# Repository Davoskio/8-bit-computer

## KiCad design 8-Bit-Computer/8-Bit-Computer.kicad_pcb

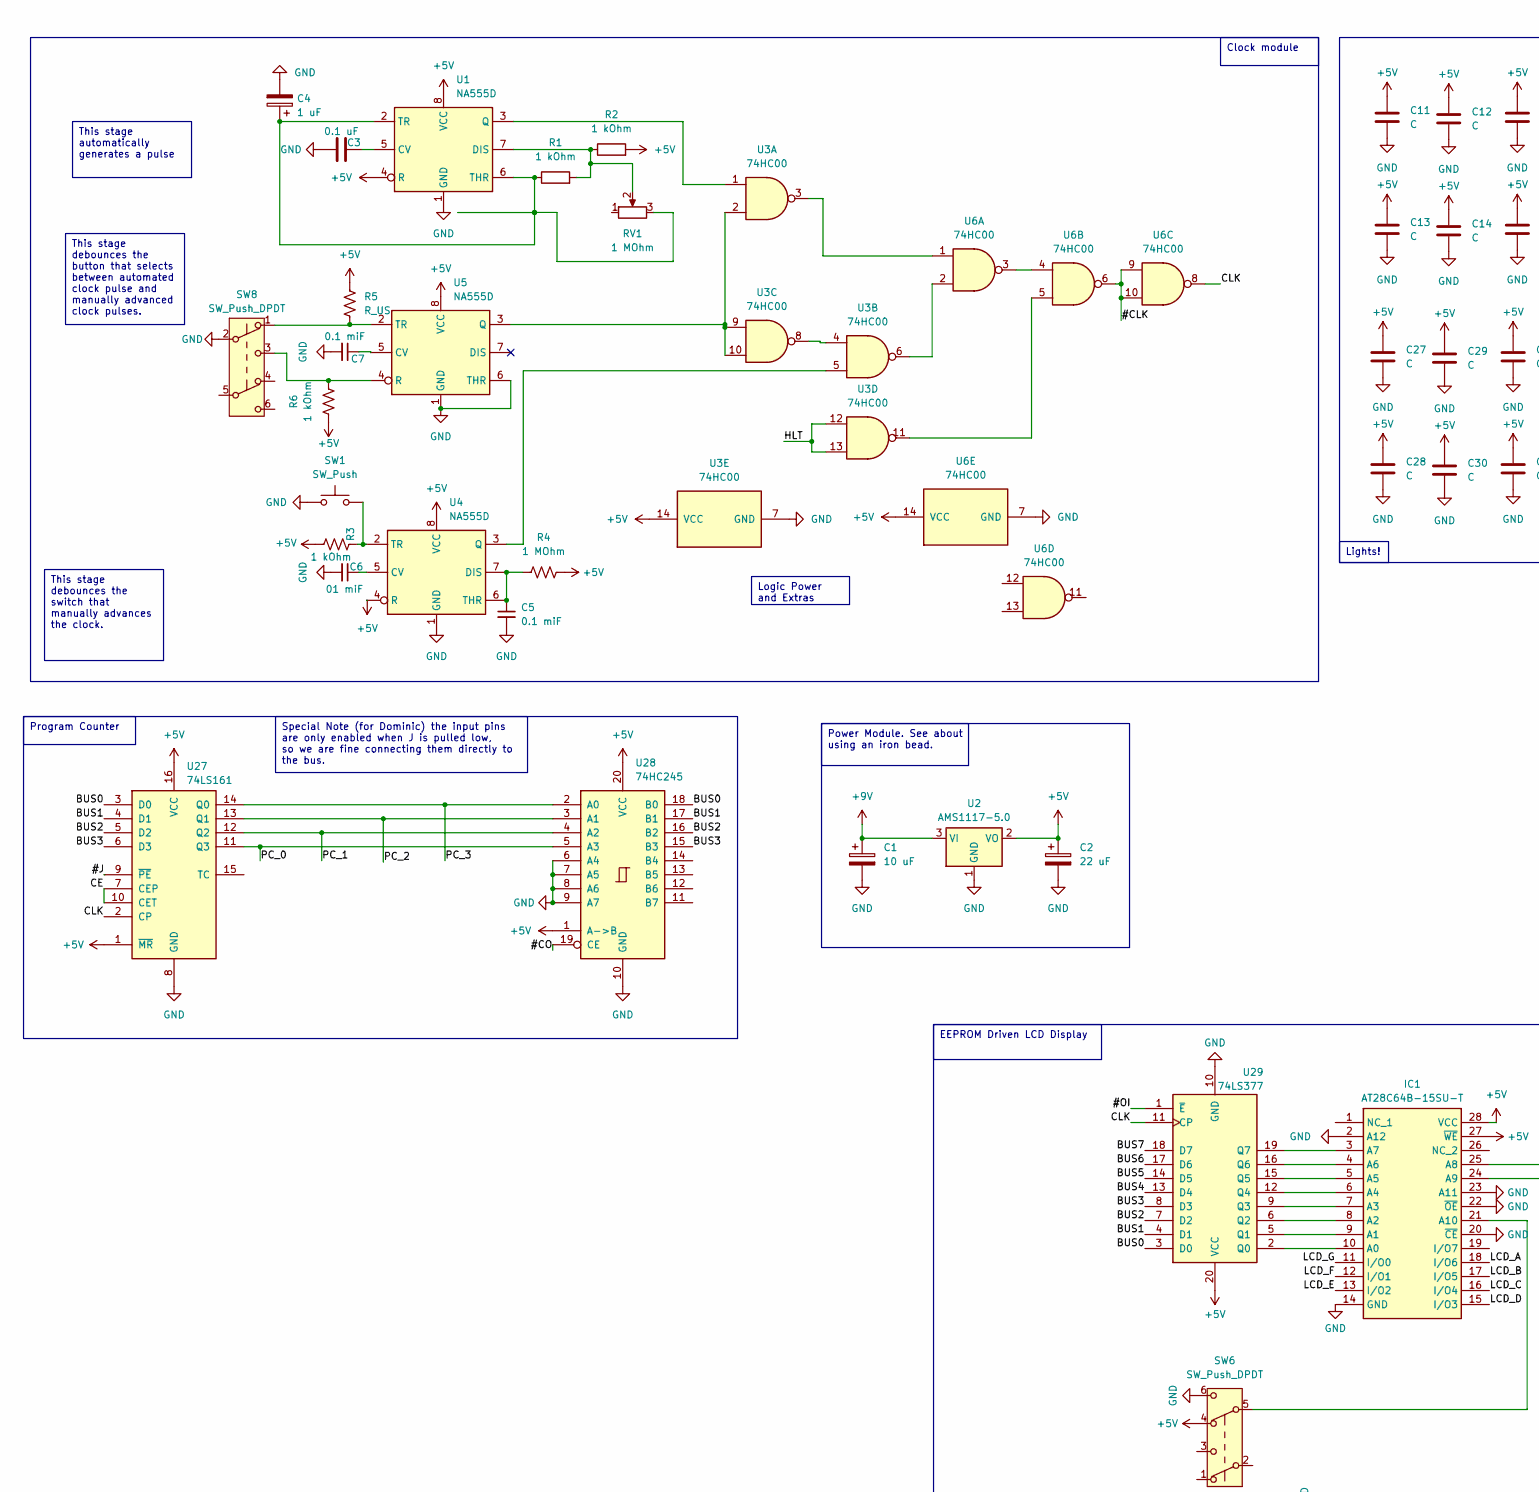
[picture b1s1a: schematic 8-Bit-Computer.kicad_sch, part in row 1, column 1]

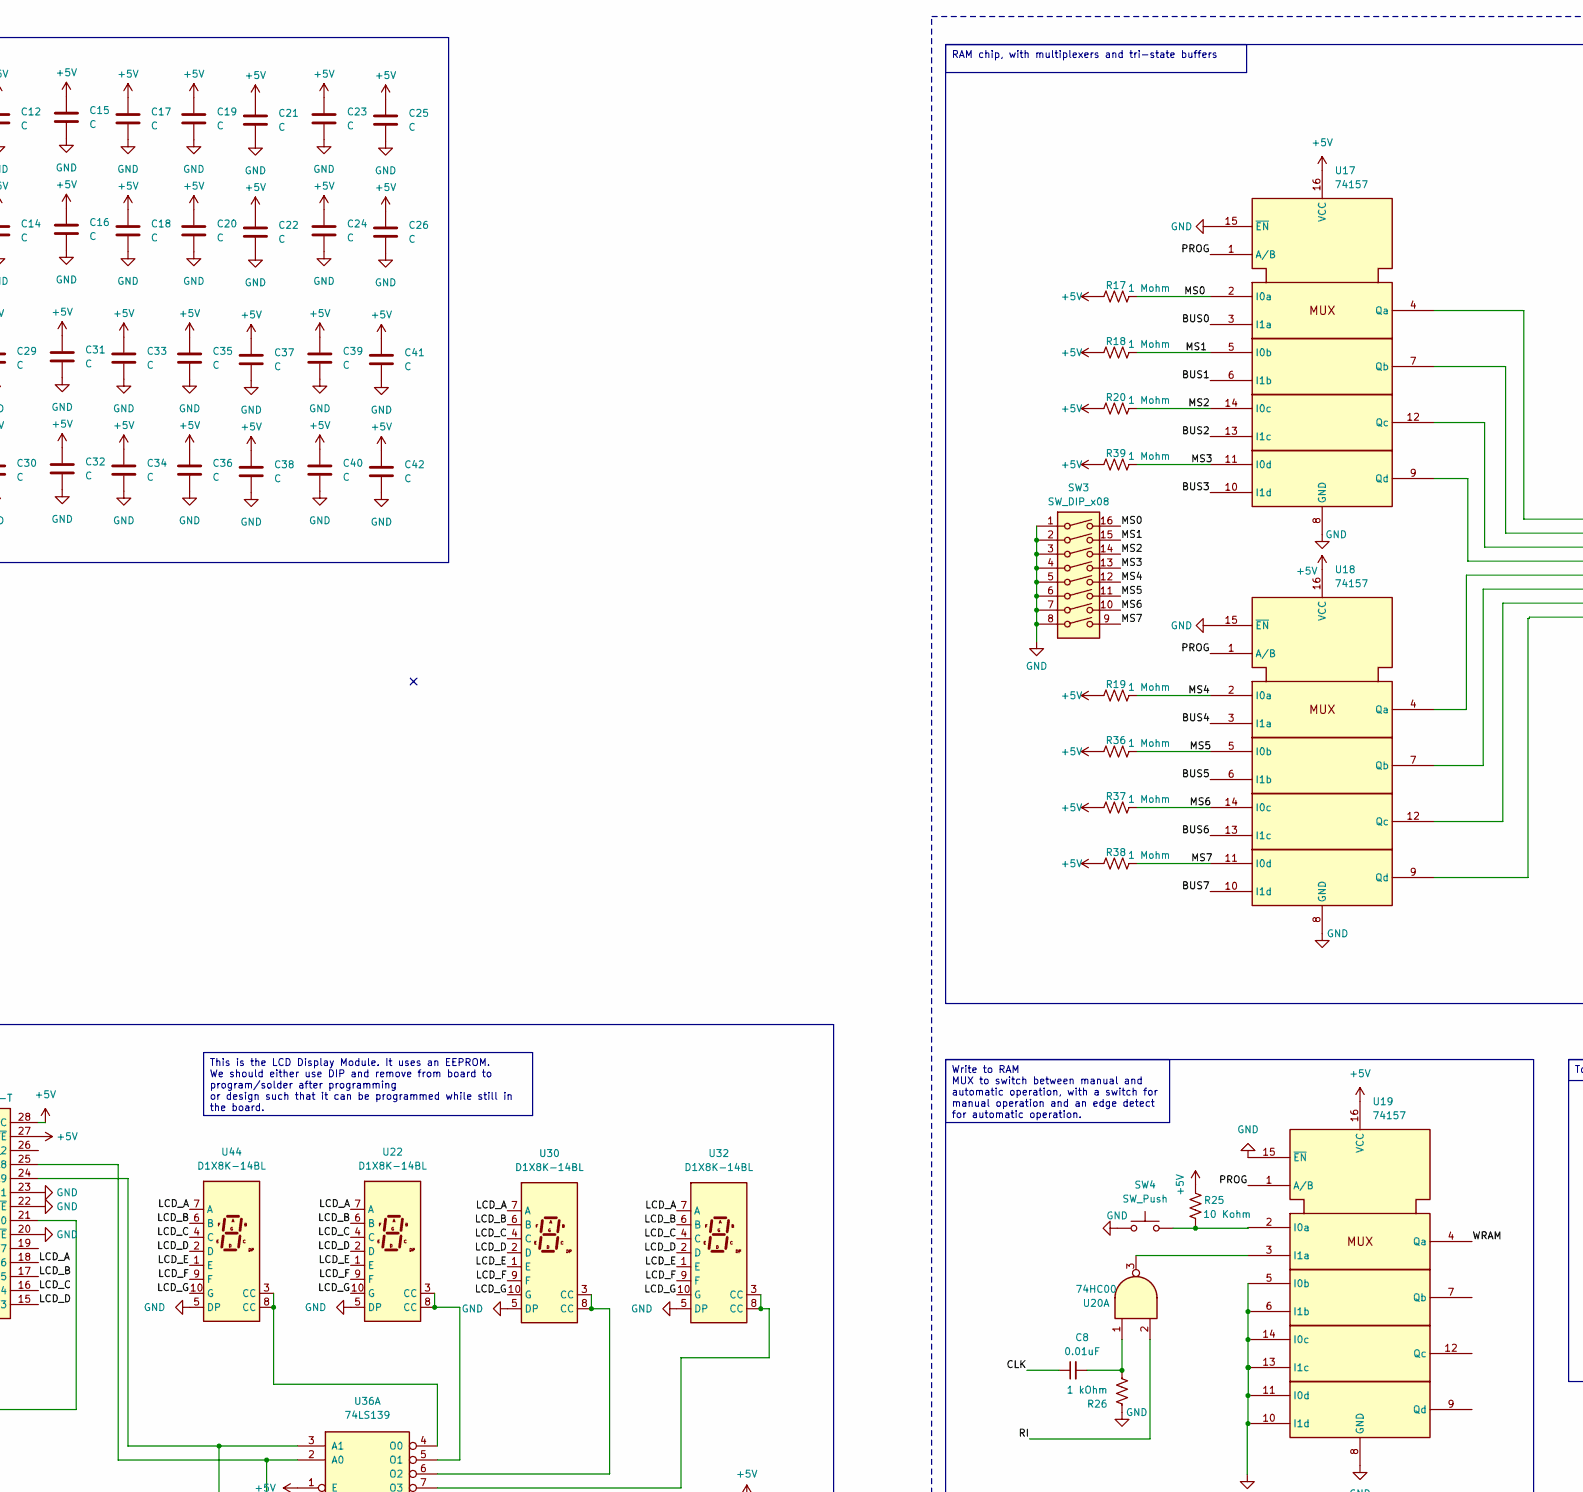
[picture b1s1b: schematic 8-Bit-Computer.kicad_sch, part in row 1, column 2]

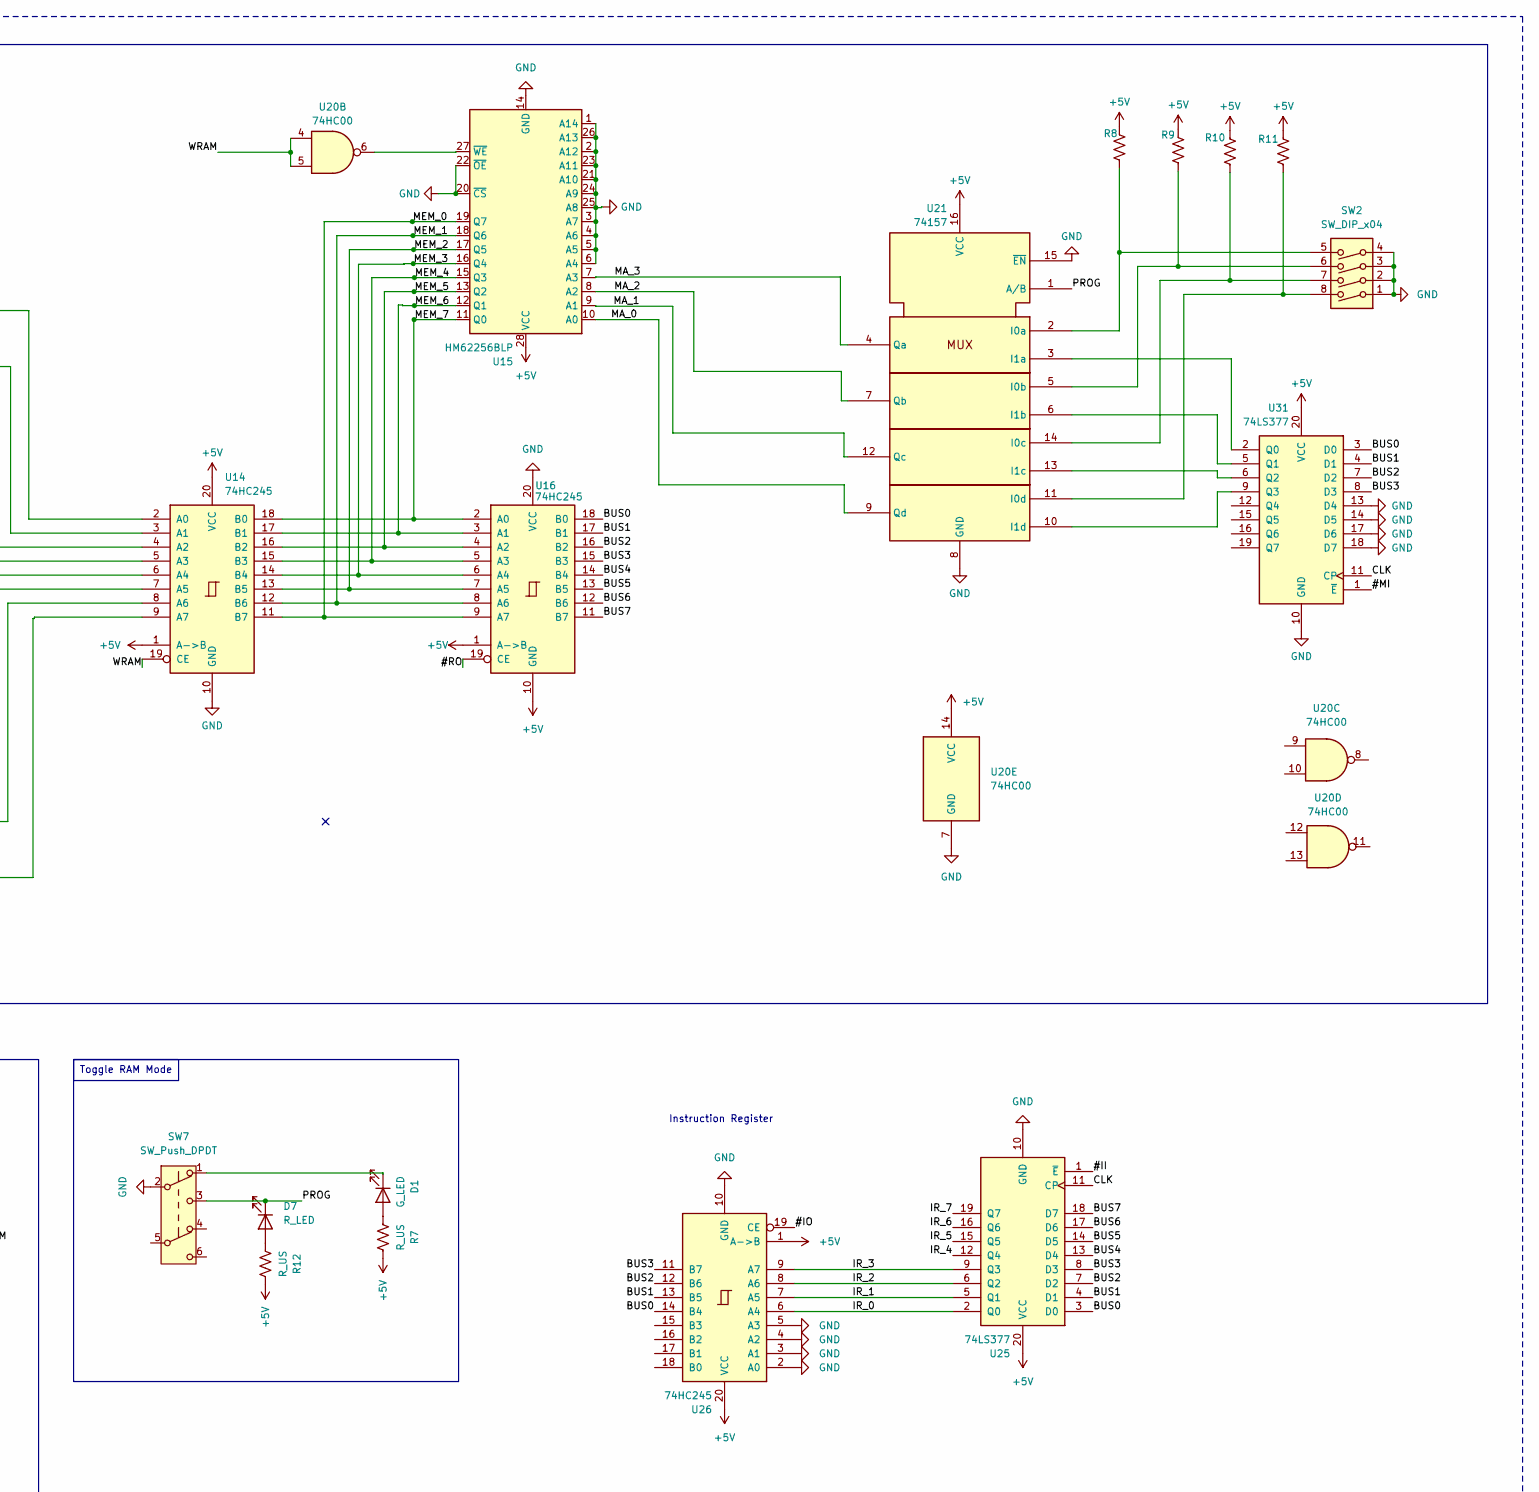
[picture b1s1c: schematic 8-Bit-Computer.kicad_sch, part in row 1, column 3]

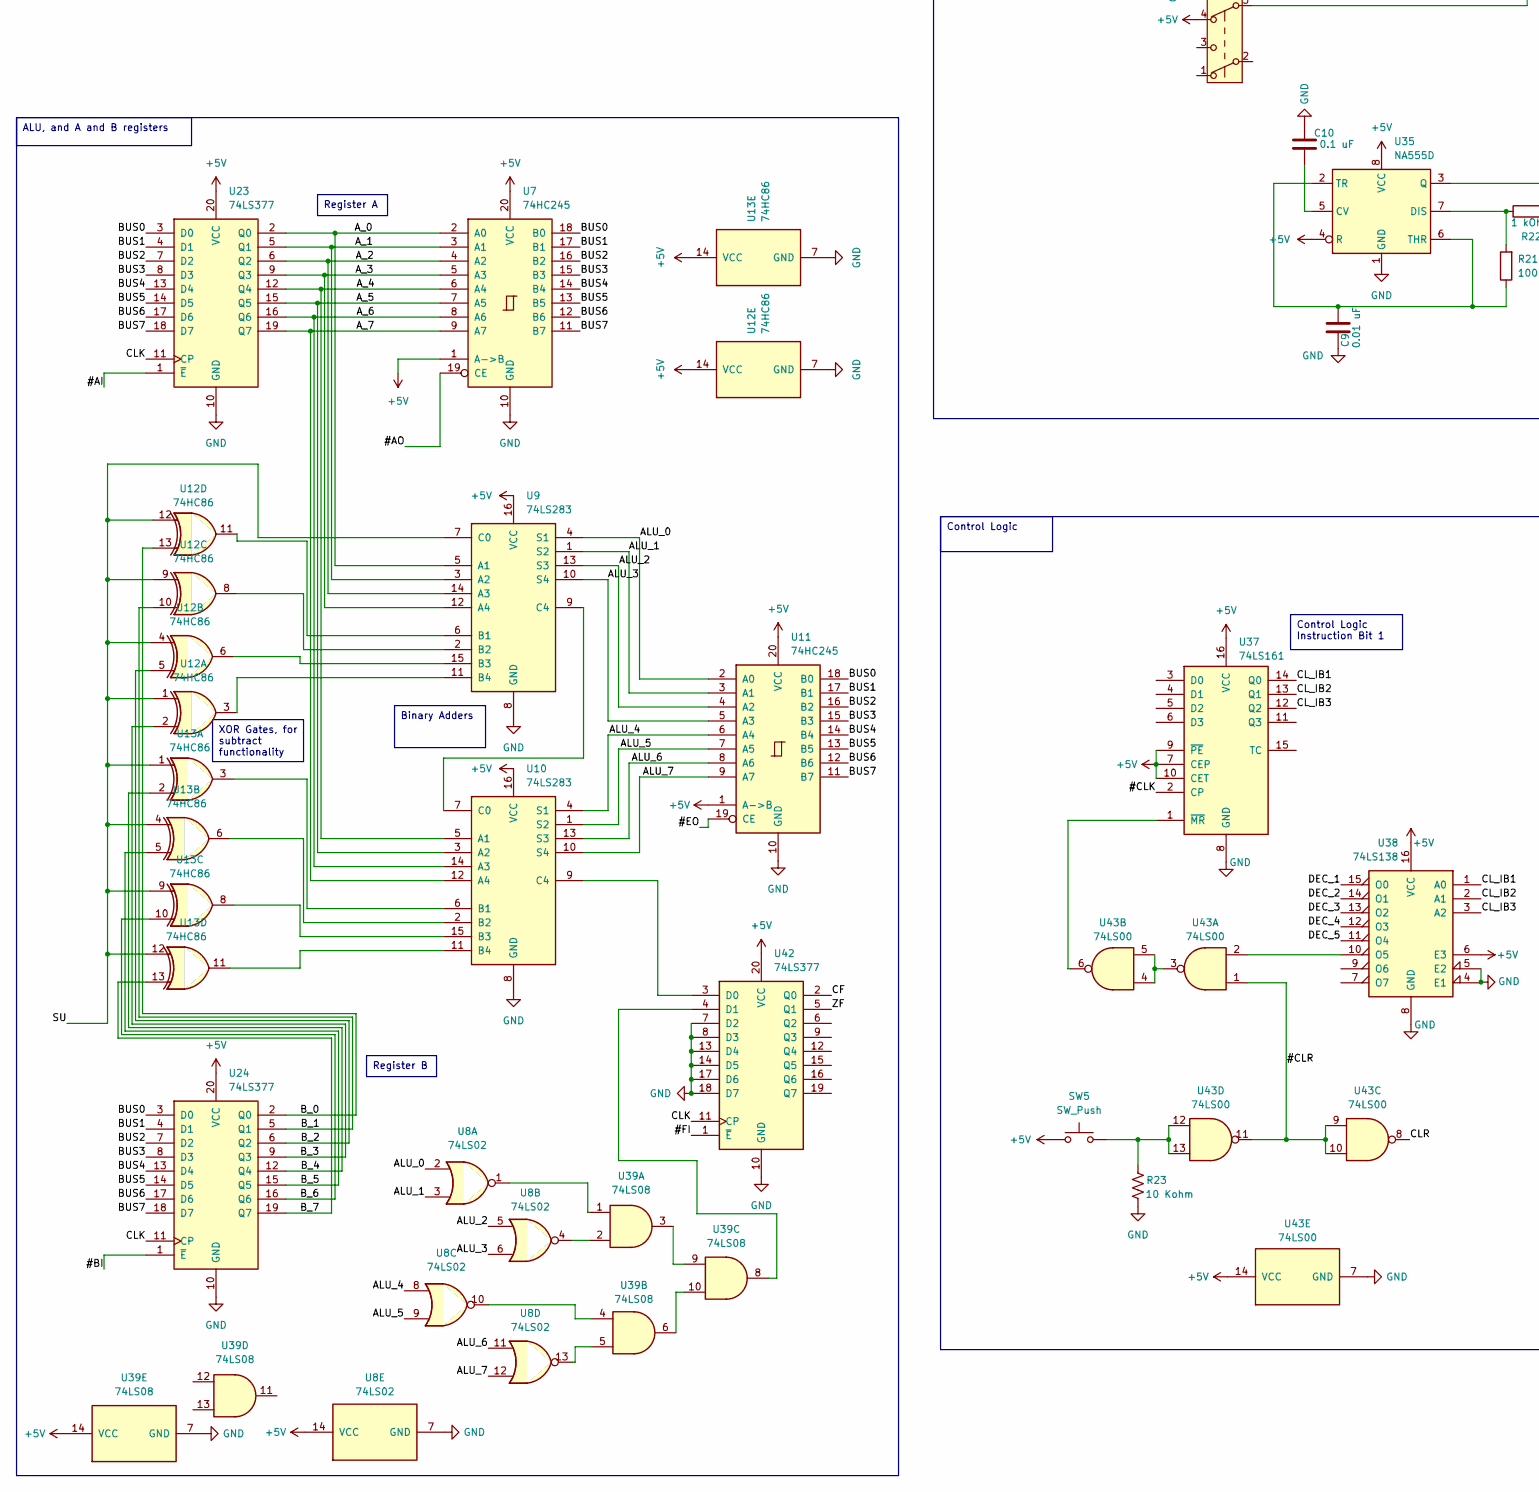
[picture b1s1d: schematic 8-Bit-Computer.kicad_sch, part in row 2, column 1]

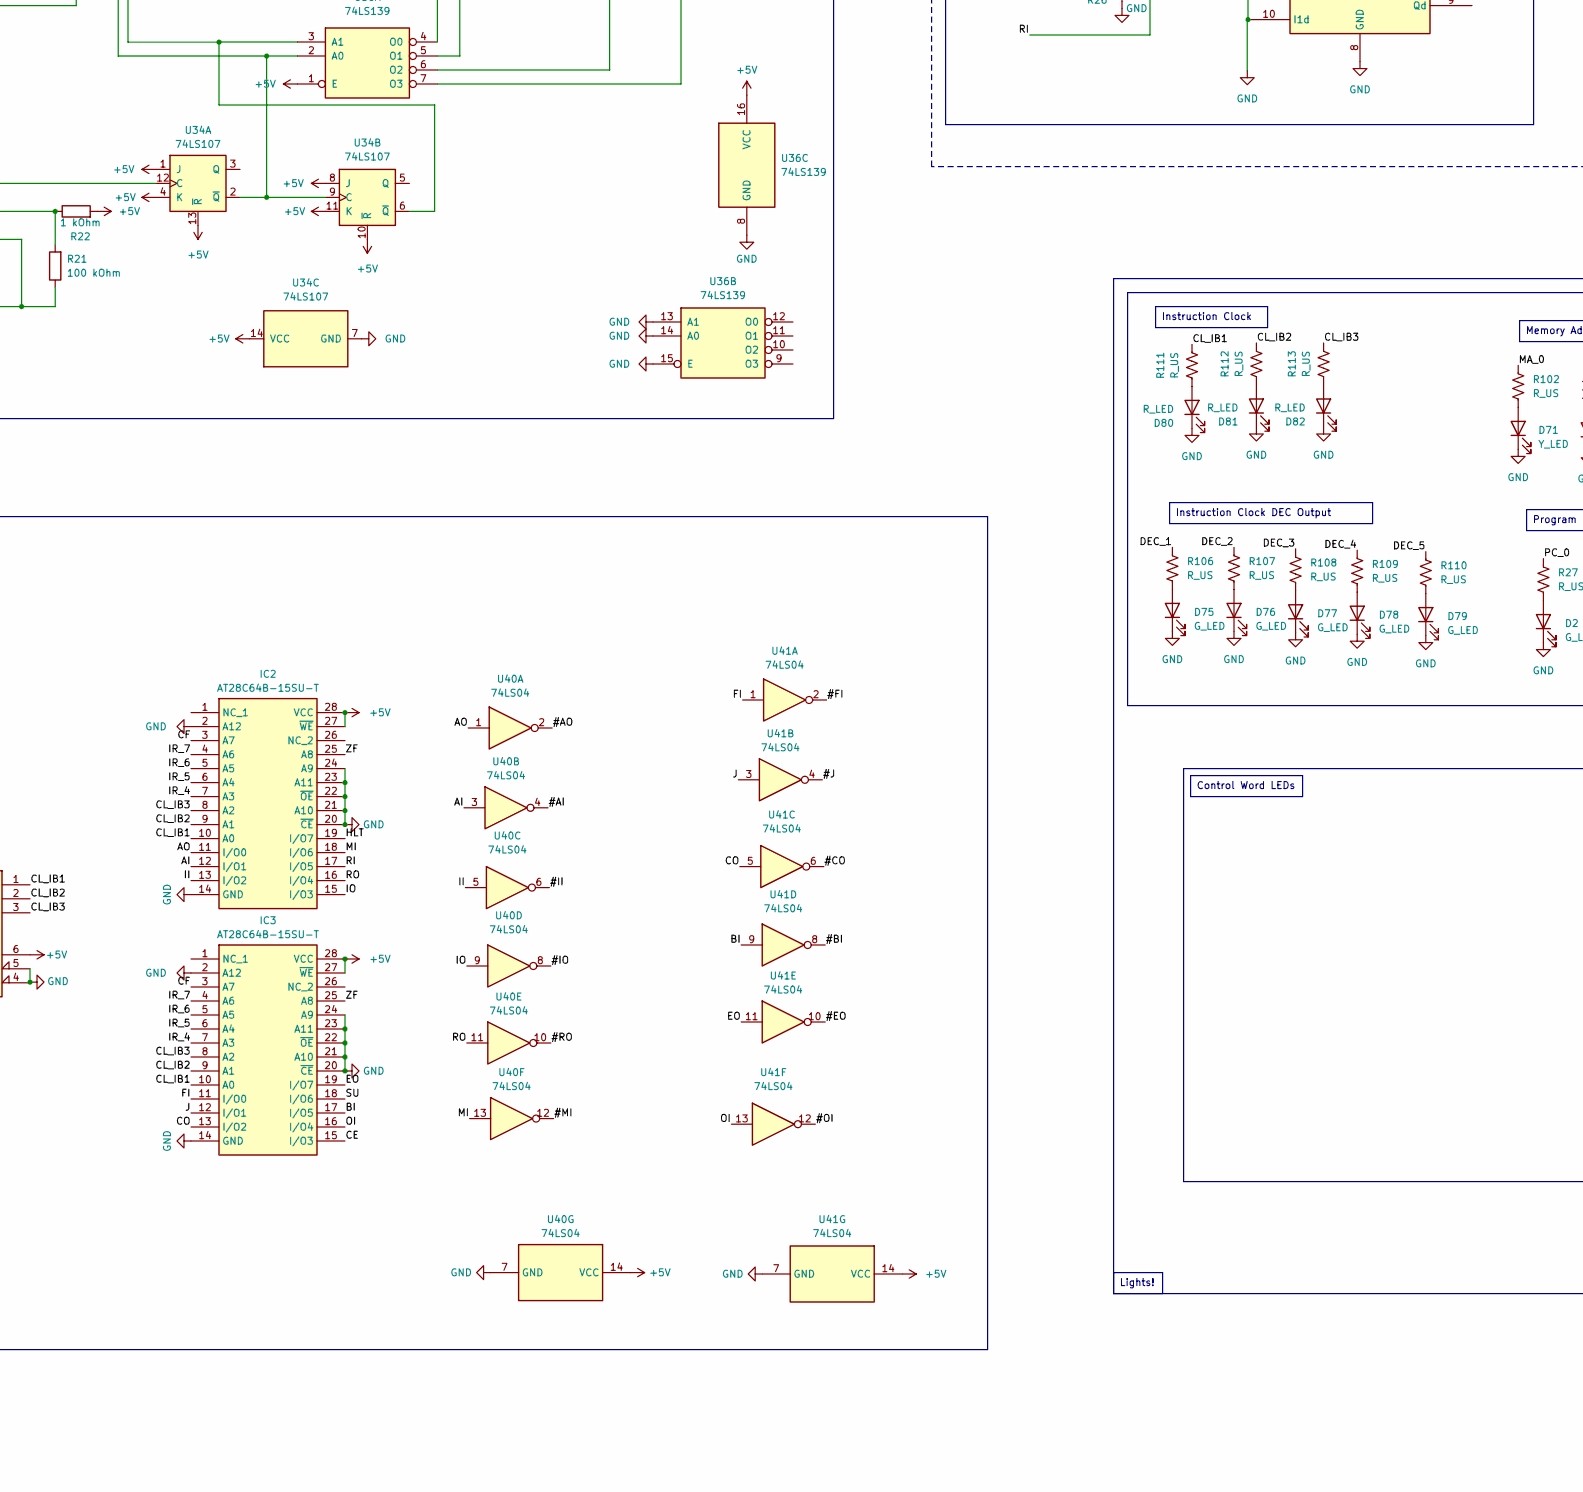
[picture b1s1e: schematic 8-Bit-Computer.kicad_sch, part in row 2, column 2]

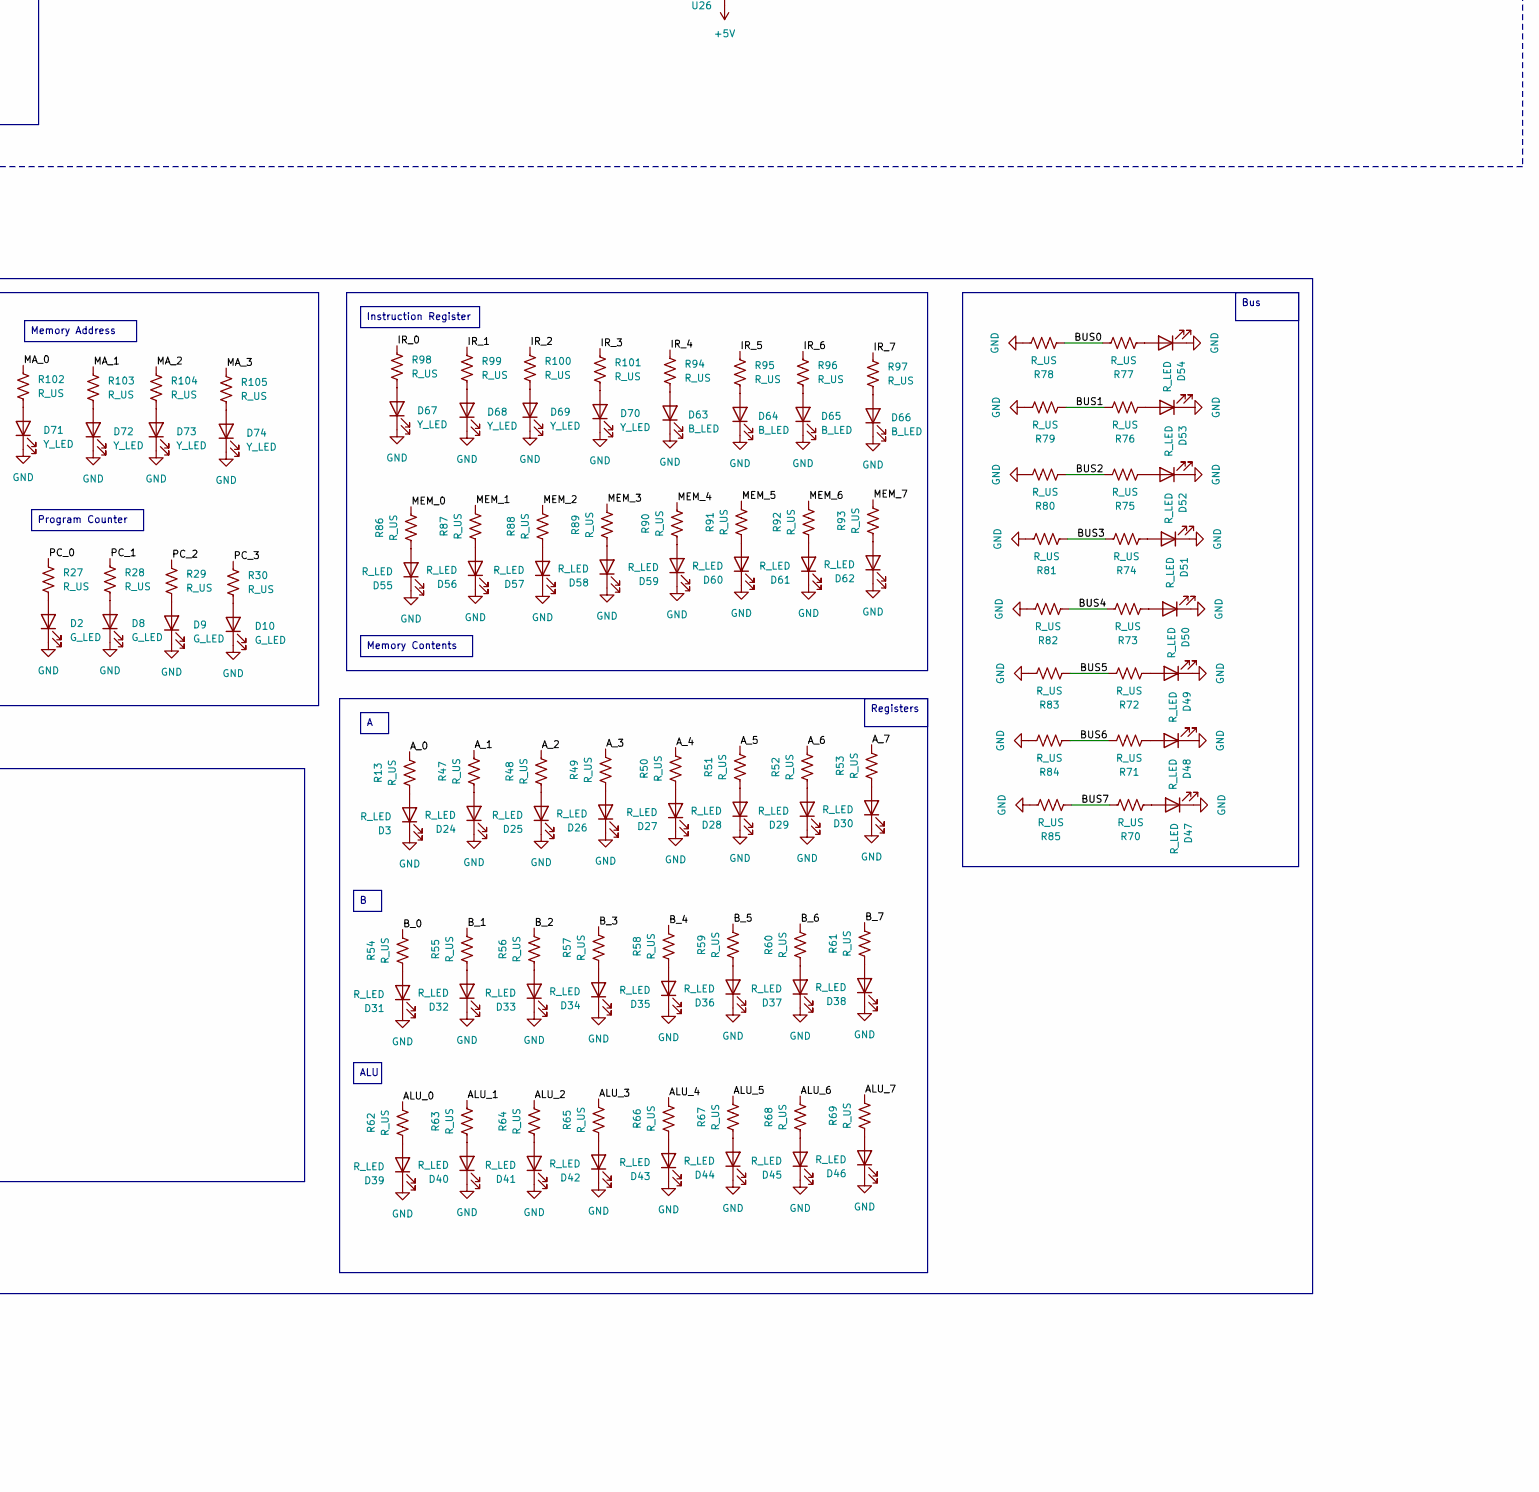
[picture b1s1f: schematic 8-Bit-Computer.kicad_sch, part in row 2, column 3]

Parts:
C1: 10 uF; C_0603_1608Metric
C2: 22 uF; C_0805_2012Metric
C3, C10: 0.1 uF; C_0402_1005Metric
C4: 1 uF; C_0402_1005Metric
C5, C7: 0.1 miF; C_0402_1005Metric
C6: 01 miF; C_0402_1005Metric
C8: 0.01uF; C_0402_1005Metric
C9: 0.01 uF; C_0402_1005Metric
C11, C12, C13, C14, C15, C16, C17, C18, C19, C20, C21, C22, C23, C24, C25, C26, C27, C28, C29, C30, C31, C32, C33, C34, C35, C36, C37, C38, C39, C40, C41, C42: C; C_0402_1005Metric
D1, D2, D8, D9, D10, D75, D76, D77, D78, D79: G_LED; LED_0805_2012Metric
D3, D7, D24, D25, D26, D27, D28, D29, D30, D31, D32, D33, D34, D35, D36, D37, D38, D39, D40, D41, D42, D43, D44, D45, D46, D47, D48, D49, D50, D51, D52, D53, D54, D55, D56, D57, D58, D59, D60, D61, D62, D80, D81, D82: R_LED; LED_0805_2012Metric
D63, D64, D65, D66: B_LED; LED_0805_2012Metric
D67, D68, D69, D70, D71, D72, D73, D74: Y_LED; LED_0805_2012Metric
IC1, IC2, IC3: AT28C64B-15SU-T; DIP-28_W15.24mm_Socket; Mouser Part Number 556-AT28C64B-15SU-T
R1, R2, R3, R6, R22, R26: 1 kOhm; R_0402_1005Metric
R4: 1 MOhm; R_0402_1005Metric
R5, R7, R8, R9, R10, R11, R12, R13, R27, R28, R29, R30, R47, R48, R49, R50, R51, R52, R53, R54, R55, R56, R57, R58, R59, R60, R61, R62, R63, R64, R65, R66, R67, R68, R69, R70, R71, R72, R73, R74, R75, R76, R77, R78, R79, R80, R81, R82, R83, R84, R85, R86, R87, R88, R89, R90, R91, R92, R93, R94, R95, R96, R97, R98, R99, R100, R101, R102, R103, R104, R105, R106, R107, R108, R109, R110, R111, R112, R113: R_US; R_0402_1005Metric
R17, R18, R19, R20, R36, R37, R38, R39: 1 Mohm; R_0402_1005Metric
R21: 100 kOhm; R_0402_1005Metric
R23, R25: 10 Kohm; R_0402_1005Metric
RV1: 1 MOhm; Potentiometer_Bourns_3314G_Vertical
SW1, SW4, SW5: SW_Push; SW_PUSH_6mm
SW2: SW_DIP_x04; SW_DIP_SPSTx04_Slide_KingTek_DSHP04TJ_W5.25mm_P1.27mm_JPin
SW3: SW_DIP_x08; SW_DIP_SPSTx08_Slide_KingTek_DSHP08TJ_W5.25mm_P1.27mm_JPin
SW6, SW7, SW8: SW_Push_DPDT; SW_Push_2P2T_Toggle_CK_PVA2xxH4xxxxxxV2
U1, U4, U5, U35: NA555D; SOP-8_3.9x4.9mm_P1.27mm
U2: AMS1117-5.0; SOT-223-3_TabPin2
U3, U6, U20: 74HC00; SOIC-14_3.9x8.7mm_P1.27mm
U7, U11, U14, U16, U26, U28: 74HC245; SOIC-20W_7.5x12.8mm_P1.27mm
U8: 74LS02; SOIC-14_3.9x8.7mm_P1.27mm
U9, U10: 74LS283; DIP-16_W7.62mm_Socket
U12, U13: 74HC86; SOIC-14_3.9x8.7mm_P1.27mm
U15: HM62256BLP; DIP-28_W15.24mm
U17, U18, U19, U21: 74157; SOIC-16_3.9x9.9mm_P1.27mm
U22, U30, U32, U44: D1X8K-14BL; D1X8K
U23, U24, U25, U29, U31, U42: 74LS377; TSSOP-20_4.4x6.5mm_P0.65mm
U27, U37: 74LS161; SOIC-16_3.9x9.9mm_P1.27mm
U34: 74LS107; SOIC-14_3.9x8.7mm_P1.27mm
U36: 74LS139; SOIC-16_3.9x9.9mm_P1.27mm
U38: 74LS138; SOIC-16_3.9x9.9mm_P1.27mm
U39: 74LS08; SOIC-14_3.9x8.7mm_P1.27mm
U40, U41: 74LS04; SOIC-14_3.9x8.7mm_P1.27mm
U43: 74LS00; SOIC-14_3.9x8.7mm_P1.27mm

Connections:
+5V: C2.1, C11.1, C12.1, C13.1, C14.1, C15.1, C16.1, C17.1, C18.1, C19.1, C20.1, C21.1, C22.1, C23.1, C24.1, C25.1, C26.1, C27.1, C28.1, C29.1, C30.1, C31.1, C32.1, C33.1, C34.1, C35.1, C36.1, C37.1, C38.1, C39.1, C40.1, C41.1, C42.1, IC1.27 (~WE), IC1.28 (VCC), IC2.27 (~WE), IC2.28 (VCC), IC3.27 (~WE), IC3.28 (VCC), R2.2, R3.1, R4.2, R5.1, R6.1, R7.2, R8.2, R9.2, R10.2, R11.2, R12.2, R17.2, R18.2, R19.2, R20.2, R22.2, R25.2, R36.2, R37.2, R38.2, R39.2, SW5.1, SW6.4 (A), U1.4 (R), U1.8 (VCC), U2.2 (VO), U3.14 (VCC), U4.4 (R), U4.8 (VCC), U5.8 (VCC), U6.14 (VCC), U7.1 (A->B), U7.20 (VCC), U8.14 (VCC), U9.16 (VCC), U10.16 (VCC), U11.1 (A->B), U11.20 (VCC), U12.14 (VCC), U13.14 (VCC), U14.1 (A->B), U14.20 (VCC), U15.28 (VCC), U16.1 (A->B), U16.10 (GND), U17.16 (VCC), U18.16 (VCC), U19.16 (VCC), U20.14 (VCC), U21.16 (VCC), U23.20 (VCC), U24.20 (VCC), U25.20 (VCC), U26.1 (A->B), U26.20 (VCC), U27.1 (~MR), U27.16 (VCC), U28.1 (A->B), U28.20 (VCC), U29.20 (VCC), U31.20 (VCC), U34.1 (J), U34.4 (K), U34.8 (J), U34.10 (~R), U34.11 (K), U34.13 (~R), U34.14 (VCC), U35.4 (R), U35.8 (VCC), U36.1 (E), U36.16 (VCC), U37.7 (CEP), U37.9 (~PE), U37.10 (CET), U37.16 (VCC), U38.6 (E3), U38.16 (VCC), U39.14 (VCC), U40.14 (VCC), U41.14 (VCC), U42.20 (VCC), U43.14 (VCC)
+9V: C1.1, U2.3 (VI)
/#AI: U23.1 (~E), U40.4
/#AO: U7.19 (CE), U40.2
/#BI: U24.1 (~E), U41.8
/#CLK: U6.6, U6.9, U6.10, U37.2 (CP)
/#CLR: U43.1, U43.9, U43.10, U43.11
/#CO: U28.19 (CE), U41.6
/#EO: U11.19 (CE), U41.10
/#FI: U41.2, U42.1 (~E)
/#II: U25.1 (~E), U40.6
/#IO: U26.19 (CE), U40.8
/#J: U27.9 (~PE), U41.4
/#MI: U31.1 (~E), U40.12
/#OI: U29.1 (~E), U41.12
/#RO: U16.19 (CE), U40.10
/AI: IC2.12 (I/O1), U40.3
/ALU_0: R62.2, U8.2, U9.4 (S1), U11.2 (A0)
/ALU_1: R63.2, U8.3, U9.1 (S2), U11.3 (A1)
/ALU_2: R64.2, U8.5, U9.13 (S3), U11.4 (A2)
/ALU_3: R65.2, U8.6, U9.10 (S4), U11.5 (A3)
/ALU_4: R66.2, U8.8, U10.4 (S1), U11.6 (A4)
/ALU_5: R67.2, U8.9, U10.1 (S2), U11.7 (A5)
/ALU_6: R68.2, U8.11, U10.13 (S3), U11.8 (A6)
/ALU_7: R69.2, U8.12, U10.10 (S4), U11.9 (A7)
/AO: IC2.11 (I/O0), U40.1
/A_0: R13.2, U7.2 (A0), U9.5 (A1), U23.2 (Q0)
/A_1: R47.2, U7.3 (A1), U9.3 (A2), U23.5 (Q1)
/A_2: R48.2, U7.4 (A2), U9.14 (A3), U23.6 (Q2)
/A_3: R49.2, U7.5 (A3), U9.12 (A4), U23.9 (Q3)
/A_4: R50.2, U7.6 (A4), U10.5 (A1), U23.12 (Q4)
/A_5: R51.2, U7.7 (A5), U10.3 (A2), U23.15 (Q5)
/A_6: R52.2, U7.8 (A6), U10.14 (A3), U23.16 (Q6)
/A_7: R53.2, U7.9 (A7), U10.12 (A4), U23.19 (Q7)
/BI: IC3.17 (I/O5), U41.9
/BUS0: R77.2, R78.1, U7.18 (B0), U11.18 (B0), U16.18 (B0), U17.3 (I1a), U23.3 (D0), U24.3 (D0), U25.3 (D0), U26.14 (B4), U27.3 (D0), U28.18 (B0), U29.3 (D0), U31.3 (D0)
/BUS1: R76.2, R79.1, U7.17 (B1), U11.17 (B1), U16.17 (B1), U17.6 (I1b), U23.4 (D1), U24.4 (D1), U25.4 (D1), U26.13 (B5), U27.4 (D1), U28.17 (B1), U29.4 (D1), U31.4 (D1)
/BUS2: R75.2, R80.1, U7.16 (B2), U11.16 (B2), U16.16 (B2), U17.13 (I1c), U23.7 (D2), U24.7 (D2), U25.7 (D2), U26.12 (B6), U27.5 (D2), U28.16 (B2), U29.7 (D2), U31.7 (D2)
/BUS3: R74.2, R81.1, U7.15 (B3), U11.15 (B3), U16.15 (B3), U17.10 (I1d), U23.8 (D3), U24.8 (D3), U25.8 (D3), U26.11 (B7), U27.6 (D3), U28.15 (B3), U29.8 (D3), U31.8 (D3)
/BUS4: R73.2, R82.1, U7.14 (B4), U11.14 (B4), U16.14 (B4), U18.3 (I1a), U23.13 (D4), U24.13 (D4), U25.13 (D4), U29.13 (D4)
/BUS5: R72.2, R83.1, U7.13 (B5), U11.13 (B5), U16.13 (B5), U18.6 (I1b), U23.14 (D5), U24.14 (D5), U25.14 (D5), U29.14 (D5)
/BUS6: R71.2, R84.1, U7.12 (B6), U11.12 (B6), U16.12 (B6), U18.13 (I1c), U23.17 (D6), U24.17 (D6), U25.17 (D6), U29.17 (D6)
/BUS7: R70.2, R85.1, U7.11 (B7), U11.11 (B7), U16.11 (B7), U18.10 (I1d), U23.18 (D7), U24.18 (D7), U25.18 (D7), U29.18 (D7)
/B_0: R54.2, U12.13, U24.2 (Q0)
/B_1: R55.2, U12.10, U24.5 (Q1)
/B_2: R56.2, U12.5, U24.6 (Q2)
/B_3: R57.2, U12.2, U24.9 (Q3)
/B_4: R58.2, U13.2, U24.12 (Q4)
/B_5: R59.2, U13.5, U24.15 (Q5)
/B_6: R60.2, U13.10, U24.16 (Q6)
/B_7: R61.2, U13.13, U24.19 (Q7)
/CE: IC3.15 (I/O3), U27.7 (CEP), U27.10 (CET)
/CF: IC2.3 (A7), IC3.3 (A7), U42.2 (Q0)
/CLK: C8.1, U6.8, U23.11 (CP), U24.11 (CP), U25.11 (CP), U27.2 (CP), U29.11 (CP), U31.11 (CP), U42.11 (CP)
/CLR: U43.8
/CL_IB1: IC2.10 (A0), IC3.10 (A0), R111.2, U37.14 (Q0), U38.1 (A0)
/CL_IB2: IC2.9 (A1), IC3.9 (A1), R112.2, U37.13 (Q1), U38.2 (A1)
/CL_IB3: IC2.8 (A2), IC3.8 (A2), R113.2, U37.12 (Q2), U38.3 (A2)
/CO: IC3.13 (I/O2), U41.5
/DEC_1: R106.1, U38.15 (O0)
/DEC_2: R107.1, U38.14 (O1)
/DEC_3: R108.1, U38.13 (O2)
/DEC_4: R109.1, U38.12 (O3)
/DEC_5: R110.1, U38.11 (O4)
/EO: IC3.19 (I/O7), U41.11
/FI: IC3.11 (I/O0), U41.1
/HLT: IC2.19 (I/O7), U3.12, U3.13
/II: IC2.13 (I/O2), U40.5
/IO: IC2.15 (I/O3), U40.9
/IR_0: R98.1, U25.2 (Q0), U26.6 (A4)
/IR_1: R99.1, U25.5 (Q1), U26.7 (A5)
/IR_2: R100.1, U25.6 (Q2), U26.8 (A6)
/IR_3: R101.1, U25.9 (Q3), U26.9 (A7)
/IR_4: IC2.7 (A3), IC3.7 (A3), R94.1, U25.12 (Q4)
/IR_5: IC2.6 (A4), IC3.6 (A4), R95.1, U25.15 (Q5)
/IR_6: IC2.5 (A5), IC3.5 (A5), R96.1, U25.16 (Q6)
/IR_7: IC2.4 (A6), IC3.4 (A6), R97.1, U25.19 (Q7)
/J: IC3.12 (I/O1), U41.3
/LCD_A: IC1.18 (I/O6), U22.7 (A), U30.7 (A), U32.7 (A), U44.7 (A)
/LCD_B: IC1.17 (I/O5), U22.6 (B), U30.6 (B), U32.6 (B), U44.6 (B)
/LCD_C: IC1.16 (I/O4), U22.4 (C), U30.4 (C), U32.4 (C), U44.4 (C)
/LCD_D: IC1.15 (I/O3), U22.2 (D), U30.2 (D), U32.2 (D), U44.2 (D)
/LCD_E: IC1.13 (I/O2), U22.1 (E), U30.1 (E), U32.1 (E), U44.1 (E)
/LCD_F: IC1.12 (I/O1), U22.9 (F), U30.9 (F), U32.9 (F), U44.9 (F)
/LCD_G: IC1.11 (I/O0), U22.10 (G), U30.10 (G), U32.10 (G), U44.10 (G)
/MA_0: R102.1, U15.10 (A0), U21.9 (Qd)
/MA_1: R103.1, U15.9 (A1), U21.12 (Qc)
/MA_2: R104.1, U15.8 (A2), U21.7 (Qb)
/MA_3: R105.1, U15.7 (A3), U21.4 (Qa)
/MEM_0: R86.2, U14.11 (B7), U15.19 (Q7), U16.9 (A7)
/MEM_1: R87.2, U14.12 (B6), U15.18 (Q6), U16.8 (A6)
/MEM_2: R88.2, U14.13 (B5), U15.17 (Q5), U16.7 (A5)
/MEM_3: R89.2, U14.14 (B4), U15.16 (Q4), U16.6 (A4)
/MEM_4: R90.2, U14.15 (B3), U15.15 (Q3), U16.5 (A3)
/MEM_5: R91.2, U14.16 (B2), U15.13 (Q2), U16.4 (A2)
/MEM_6: R92.2, U14.17 (B1), U15.12 (Q1), U16.3 (A1)
/MEM_7: R93.2, U14.18 (B0), U15.11 (Q0), U16.2 (A0)
/MI: IC2.18 (I/O6), U40.13
/MS0: R17.1, SW3.16, U17.2 (I0a)
/MS1: R18.1, SW3.15, U17.5 (I0b)
/MS2: R20.1, SW3.14, U17.14 (I0c)
/MS3: R39.1, SW3.13, U17.11 (I0d)
/MS4: R19.1, SW3.12, U18.2 (I0a)
/MS5: R36.1, SW3.11, U18.5 (I0b)
/MS6: R37.1, SW3.10, U18.14 (I0c)
/MS7: R38.1, SW3.9, U18.11 (I0d)
/OI: IC3.16 (I/O4), U41.13
/PC_0: R27.1, U27.11 (Q3), U28.5 (A3)
/PC_1: R28.1, U27.12 (Q2), U28.4 (A2)
/PC_2: R29.1, U27.13 (Q1), U28.3 (A1)
/PC_3: R30.1, U27.14 (Q0), U28.2 (A0)
/PROG: D7.1 (K), SW7.3 (C), U17.1 (A/B), U18.1 (A/B), U19.1 (A/B), U21.1 (A/B)
/RO: IC2.16 (I/O4), U40.11
/SU: IC3.18 (I/O6), U9.7 (C0), U12.1, U12.4, U12.9, U12.12, U13.1, U13.4, U13.9, U13.12
/ZF: IC2.25 (A8), IC3.25 (A8), U42.5 (Q1)
GND: C1.2, C2.2, C3.1, C4.2, C5.2, C6.2, C7.2, C9.2, C10.1, C11.2, C12.2, C13.2, C14.2, C15.2, C16.2, C17.2, C18.2, C19.2, C20.2, C21.2, C22.2, C23.2, C24.2, C25.2, C26.2, C27.2, C28.2, C29.2, C30.2, C31.2, C32.2, C33.2, C34.2, C35.2, C36.2, C37.2, C38.2, C39.2, C40.2, C41.2, C42.2, D2.1 (K), D3.1 (K), D8.1 (K), D9.1 (K), D10.1 (K), D24.1 (K), D25.1 (K), D26.1 (K), D27.1 (K), D28.1 (K), D29.1 (K), D30.1 (K), D31.1 (K), D32.1 (K), D33.1 (K), D34.1 (K), D35.1 (K), D36.1 (K), D37.1 (K), D38.1 (K), D39.1 (K), D40.1 (K), D41.1 (K), D42.1 (K), D43.1 (K), D44.1 (K), D45.1 (K), D46.1 (K), D47.1 (K), D48.1 (K), D49.1 (K), D50.1 (K), D51.1 (K), D52.1 (K), D53.1 (K), D54.1 (K), D55.1 (K), D56.1 (K), D57.1 (K), D58.1 (K), D59.1 (K), D60.1 (K), D61.1 (K), D62.1 (K), D63.1 (K), D64.1 (K), D65.1 (K), D66.1 (K), D67.1 (K), D68.1 (K), D69.1 (K), D70.1 (K), D71.1 (K), D72.1 (K), D73.1 (K), D74.1 (K), D75.1 (K), D76.1 (K), D77.1 (K), D78.1 (K), D79.1 (K), D80.1 (K), D81.1 (K), D82.1 (K), IC1.2 (A12), IC1.14 (GND), IC1.20 (~CE), IC1.22 (~OE), IC1.23 (A11), IC2.2 (A12), IC2.14 (GND), IC2.20 (~CE), IC2.21 (A10), IC2.22 (~OE), IC2.23 (A11), IC2.24 (A9), IC3.2 (A12), IC3.14 (GND), IC3.20 (~CE), IC3.21 (A10), IC3.22 (~OE), IC3.23 (A11), IC3.24 (A9), R23.1, R26.2, R78.2, R79.2, R80.2, R81.2, R82.2, R83.2, R84.2, R85.2, SW1.1, SW2.1, SW2.2, SW2.3, SW2.4, SW3.1, SW3.2, SW3.3, SW3.4, SW3.5, SW3.6, SW3.7, SW3.8, SW4.1, SW6.6 (C), SW7.2 (B), SW8.2 (B), U1.1 (GND), U2.1 (GND), U3.7 (GND), U4.1 (GND), U5.1 (GND), U5.6 (THR), U6.7 (GND), U7.10 (GND), U8.7 (GND), U9.8 (GND), U10.8 (GND), U11.10 (GND), U12.7 (GND), U13.7 (GND), U14.10 (GND), U15.1 (A14), U15.2 (A12), U15.3 (A7), U15.4 (A6), U15.5 (A5), U15.6 (A4), U15.14 (GND), U15.20 (~CS), U15.21 (A10), U15.22 (~OE), U15.23 (A11), U15.24 (A9), U15.25 (A8), U15.26 (A13), U16.20 (VCC), U17.8 (GND), U17.15 (~EN), U18.8 (GND), U18.15 (~EN), U19.5 (I0b), U19.6 (I1b), U19.8 (GND), U19.10 (I1d), U19.11 (I0d), U19.13 (I1c), U19.14 (I0c), U19.15 (~EN), U20.7 (GND), U21.8 (GND), U21.15 (~EN), U22.5 (DP), U23.10 (GND), U24.10 (GND), U25.10 (GND), U26.2 (A0), U26.3 (A1), U26.4 (A2), U26.5 (A3), U26.10 (GND)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
unnamed: C8.2, R26.1, U20.1
unnamed: D1.2 (A), R7.1
unnamed: D1.1 (K), SW7.1 (A)
unnamed: D2.2 (A), R27.2
unnamed: D3.2 (A), R13.1
unnamed: D7.2 (A), R12.1
unnamed: D8.2 (A), R28.2
unnamed: D9.2 (A), R29.2
unnamed: D10.2 (A), R30.2
unnamed: D24.2 (A), R47.1
unnamed: D25.2 (A), R48.1
unnamed: D26.2 (A), R49.1
unnamed: D27.2 (A), R50.1
unnamed: D28.2 (A), R51.1
unnamed: D29.2 (A), R52.1
unnamed: D30.2 (A), R53.1
unnamed: D31.2 (A), R54.1
unnamed: D32.2 (A), R55.1
unnamed: D33.2 (A), R56.1
unnamed: D34.2 (A), R57.1
unnamed: D35.2 (A), R58.1
unnamed: D36.2 (A), R59.1
unnamed: D37.2 (A), R60.1
unnamed: D38.2 (A), R61.1
unnamed: D39.2 (A), R62.1
unnamed: D40.2 (A), R63.1
unnamed: D41.2 (A), R64.1
unnamed: D42.2 (A), R65.1
unnamed: D43.2 (A), R66.1
unnamed: D44.2 (A), R67.1
unnamed: D45.2 (A), R68.1
unnamed: D46.2 (A), R69.1
unnamed: D47.2 (A), R70.1
unnamed: D48.2 (A), R71.1
unnamed: D49.2 (A), R72.1
unnamed: D50.2 (A), R73.1
unnamed: D51.2 (A), R74.1
unnamed: D52.2 (A), R75.1
unnamed: D53.2 (A), R76.1
unnamed: D54.2 (A), R77.1
unnamed: D55.2 (A), R86.1
unnamed: D56.2 (A), R87.1
unnamed: D57.2 (A), R88.1
unnamed: D58.2 (A), R89.1
unnamed: D59.2 (A), R90.1
unnamed: D60.2 (A), R91.1
unnamed: D61.2 (A), R92.1
unnamed: D62.2 (A), R93.1
unnamed: D63.2 (A), R94.2
unnamed: D64.2 (A), R95.2
unnamed: D65.2 (A), R96.2
unnamed: D66.2 (A), R97.2
unnamed: D67.2 (A), R98.2
unnamed: D68.2 (A), R99.2
unnamed: D69.2 (A), R100.2
unnamed: D70.2 (A), R101.2
unnamed: D71.2 (A), R102.2
unnamed: D72.2 (A), R103.2
unnamed: D73.2 (A), R104.2
unnamed: D74.2 (A), R105.2
unnamed: D75.2 (A), R106.2
unnamed: D76.2 (A), R107.2
unnamed: D77.2 (A), R108.2
unnamed: D78.2 (A), R109.2
unnamed: D79.2 (A), R110.2
unnamed: D80.2 (A), R111.1
unnamed: D81.2 (A), R112.1
unnamed: D82.2 (A), R113.1
unnamed: IC1.10 (A0), U29.2 (Q0)
unnamed: IC1.9 (A1), U29.5 (Q1)
unnamed: IC1.8 (A2), U29.6 (Q2)
unnamed: IC1.7 (A3), U29.9 (Q3)
unnamed: IC1.6 (A4), U29.12 (Q4)
unnamed: IC1.5 (A5), U29.15 (Q5)
unnamed: IC1.4 (A6), U29.16 (Q6)
unnamed: IC1.3 (A7), U29.19 (Q7)
unnamed: IC1.25 (A8), U34.2 (~Q), U34.9 (C), U36.2 (A0)
unnamed: IC1.24 (A9), U34.6 (~Q), U36.3 (A1)
unnamed: IC1.21 (A10), SW6.5 (B)
unnamed: R23.2, SW5.2, U43.12, U43.13
unnamed: C3.2, U1.5 (CV)
unnamed: R1.2, R2.1, RV1.2, U1.7 (DIS)
unnamed: U1.3 (Q), U3.1
unnamed: C4.1, R1.1, RV1.3, U1.2 (TR), U1.6 (THR)
unnamed: U3.3, U6.1
unnamed: U3.4, U3.8
unnamed: U3.6, U6.2
unnamed: U3.11, U6.5
unnamed: C6.1, U4.5 (CV)
unnamed: C5.1, R4.1, U4.6 (THR), U4.7 (DIS)
unnamed: U3.5, U4.3 (Q)
unnamed: R3.2, SW1.2, U4.2 (TR)
unnamed: C7.1, U5.5 (CV)
unnamed: U3.2, U3.9, U3.10, U5.3 (Q)
unnamed: R6.2, SW8.3 (C), U5.4 (R)
unnamed: R5.2, SW8.1 (A), U5.2 (TR)
unnamed: U6.3, U6.4
unnamed: U9.6 (B1), U12.11
unnamed: U9.2 (B2), U12.8
unnamed: U9.15 (B3), U12.6
unnamed: U9.11 (B4), U12.3
unnamed: U10.6 (B1), U13.3
unnamed: U10.2 (B2), U13.6
unnamed: U10.15 (B3), U13.8
unnamed: U10.11 (B4), U13.11
unnamed: U9.9 (C4), U10.7 (C0)
unnamed: U10.9 (C4), U42.3 (D0)
unnamed: U14.2 (A0), U17.4 (Qa)
unnamed: U14.3 (A1), U17.7 (Qb)
unnamed: U14.4 (A2), U17.12 (Qc)
unnamed: U14.5 (A3), U17.9 (Qd)
unnamed: U14.6 (A4), U18.4 (Qa)
unnamed: U14.7 (A5), U18.7 (Qb)
unnamed: U14.8 (A6), U18.12 (Qc)
unnamed: U14.9 (A7), U18.9 (Qd)
unnamed: U15.27 (~WE), U20.6
unnamed: R25.1, SW4.2, U19.2 (I0a)
unnamed: U19.3 (I1a), U20.3
unnamed: R8.1, SW2.5, U21.2 (I0a)
unnamed: R9.1, SW2.6, U21.5 (I0b)
unnamed: R10.1, SW2.7, U21.14 (I0c)
unnamed: R11.1, SW2.8, U21.11 (I0d)
unnamed: U21.3 (I1a), U31.2 (Q0)
unnamed: U21.6 (I1b), U31.5 (Q1)
unnamed: U21.13 (I1c), U31.6 (Q2)
unnamed: U21.10 (I1d), U31.9 (Q3)
unnamed: U34.12 (C), U35.3 (Q)
unnamed: C10.2, U35.5 (CV)
unnamed: R21.2, R22.1, U35.7 (DIS)
unnamed: C9.1, R21.1, U35.2 (TR), U35.6 (THR)
unnamed: U36.4 (O0), U44.3 (CC), U44.8 (CC)
unnamed: U22.3 (CC), U22.8 (CC), U36.5 (O1)
unnamed: U30.3 (CC), U30.8 (CC), U36.6 (O2)
unnamed: U32.3 (CC), U32.8 (CC), U36.7 (O3)
unnamed: U37.1 (~MR), U43.6
unnamed: U38.10 (O5), U43.2
unnamed: U8.1, U39.1
unnamed: U8.4, U39.2
unnamed: U39.3, U39.9
unnamed: U8.10, U39.4
unnamed: U8.13, U39.5
unnamed: U39.6, U39.10
unnamed: U39.8, U42.4 (D1)
unnamed: U43.3, U43.4, U43.5

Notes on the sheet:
Program Counter
Control Word LEDs
EEPROM Driven LCD Display
This is the LCD Display Module. It uses an EEPROM. We should either use DIP and remove from board to program/solder after programming or design such that it can be programmed while still in the board.
Control Logic
Special Note (for Dominic) the input pins are only enabled when J is pulled low, so we are fine connecting them directly to the bus.
Clock module
Write to RAM MUX to switch between manual and automatic operation, with a switch for manual operation and an edge detect for automatic operation.
Instruction Register
Instruction Clock
This stage debounces the button that selects between automated clock pulse and manually advanced clock pulses.
Power Module. See about using an iron bead.
RAM chip, with multiplexers and tri-state buffers
ALU, and A and B registers
Lights!
Register B
XOR Gates, for subtract functionality
This stage automatically generates a pulse
Register A
Memory Address
ALU
Memory Contents
This stage debounces the switch that manually advances the clock.
Control Logic Instruction Bit 1
Toggle RAM Mode
Instruction Clock DEC Output
Binary Adders
Bus
Registers
Logic Power and Extras

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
